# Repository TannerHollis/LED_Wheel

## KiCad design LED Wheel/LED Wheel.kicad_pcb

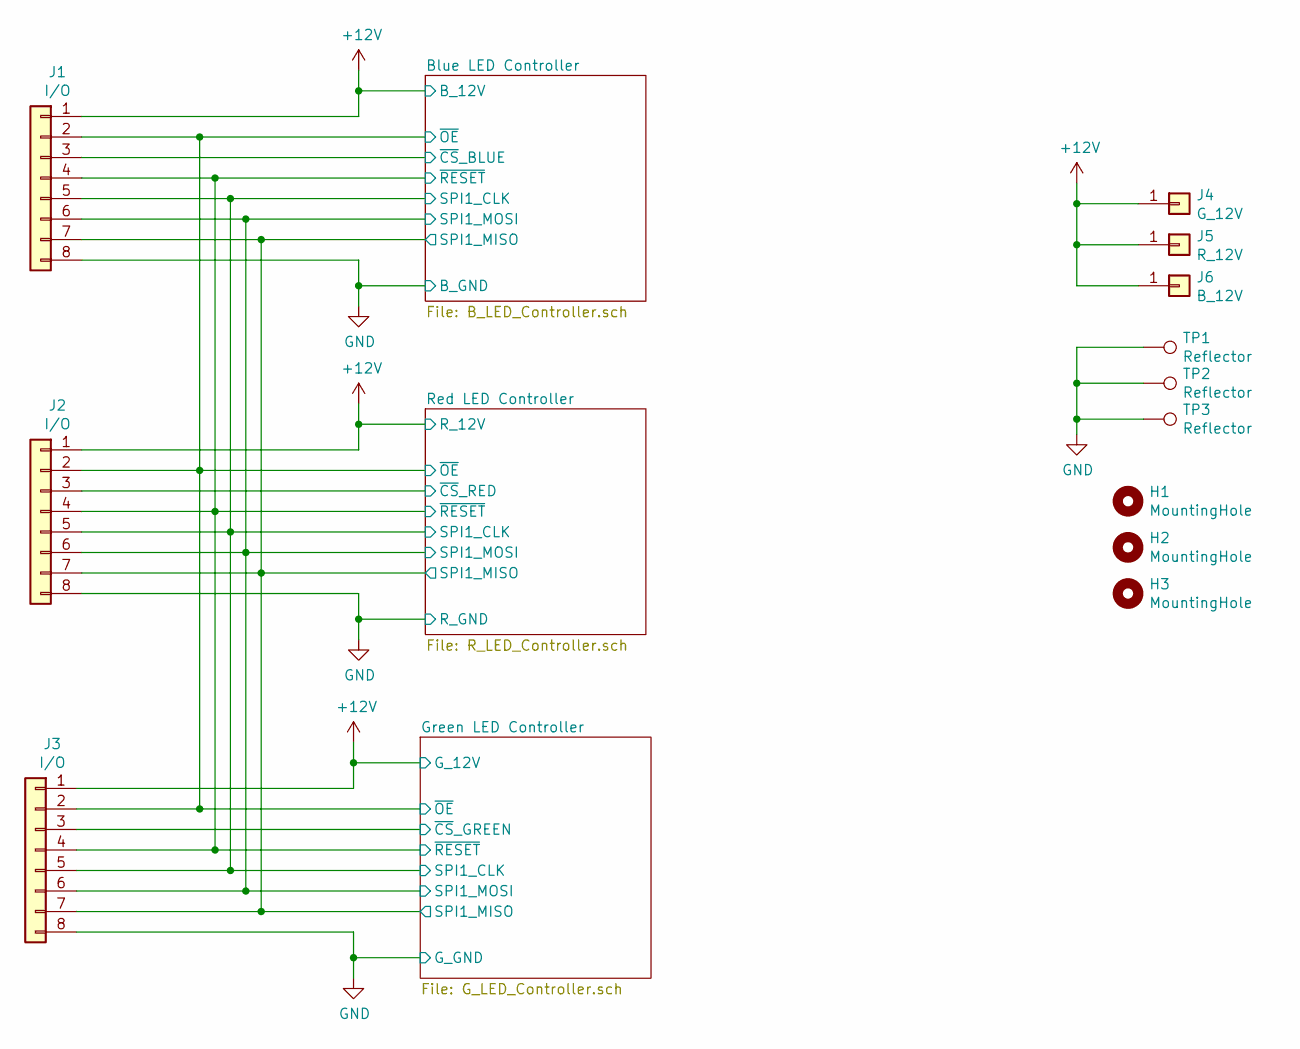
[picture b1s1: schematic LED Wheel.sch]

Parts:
H1, H2, H3: MountingHole; MountingHole_2.2mm_M2
J1, J2, J3: I/O; PinHeader_1x08_P1.27mm_Vertical
J4: G_12V; PinHeader_1x01_P2.54mm_Vertical
J5: R_12V; PinHeader_1x01_P2.54mm_Vertical
J6: B_12V; PinHeader_1x01_P2.54mm_Vertical
TP1, TP2, TP3: Reflector; Reflector 2x4mm

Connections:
+12V: J1.1, J2.1, J3.1, J4.1, J5.1, J6.1; also elsewhere on the board
/Blue LED Controller/SPI1_CLK: J1.5, J2.5, J3.5; also elsewhere on the board
/Blue LED Controller/~CS~_BLUE: J1.3; also elsewhere on the board
/Blue LED Controller/~OE~: J1.2, J2.2, J3.2; also elsewhere on the board
/Blue LED Controller/~RESET~: J1.4, J2.4, J3.4; also elsewhere on the board
/Green LED Controller/~CS~_GREEN: J3.3; also elsewhere on the board
/Red LED Controller/~CS~_RED: J2.3; also elsewhere on the board
EP: J1.8, J2.8, J3.8, TP1.1, TP2.1, TP3.1; also elsewhere on the board

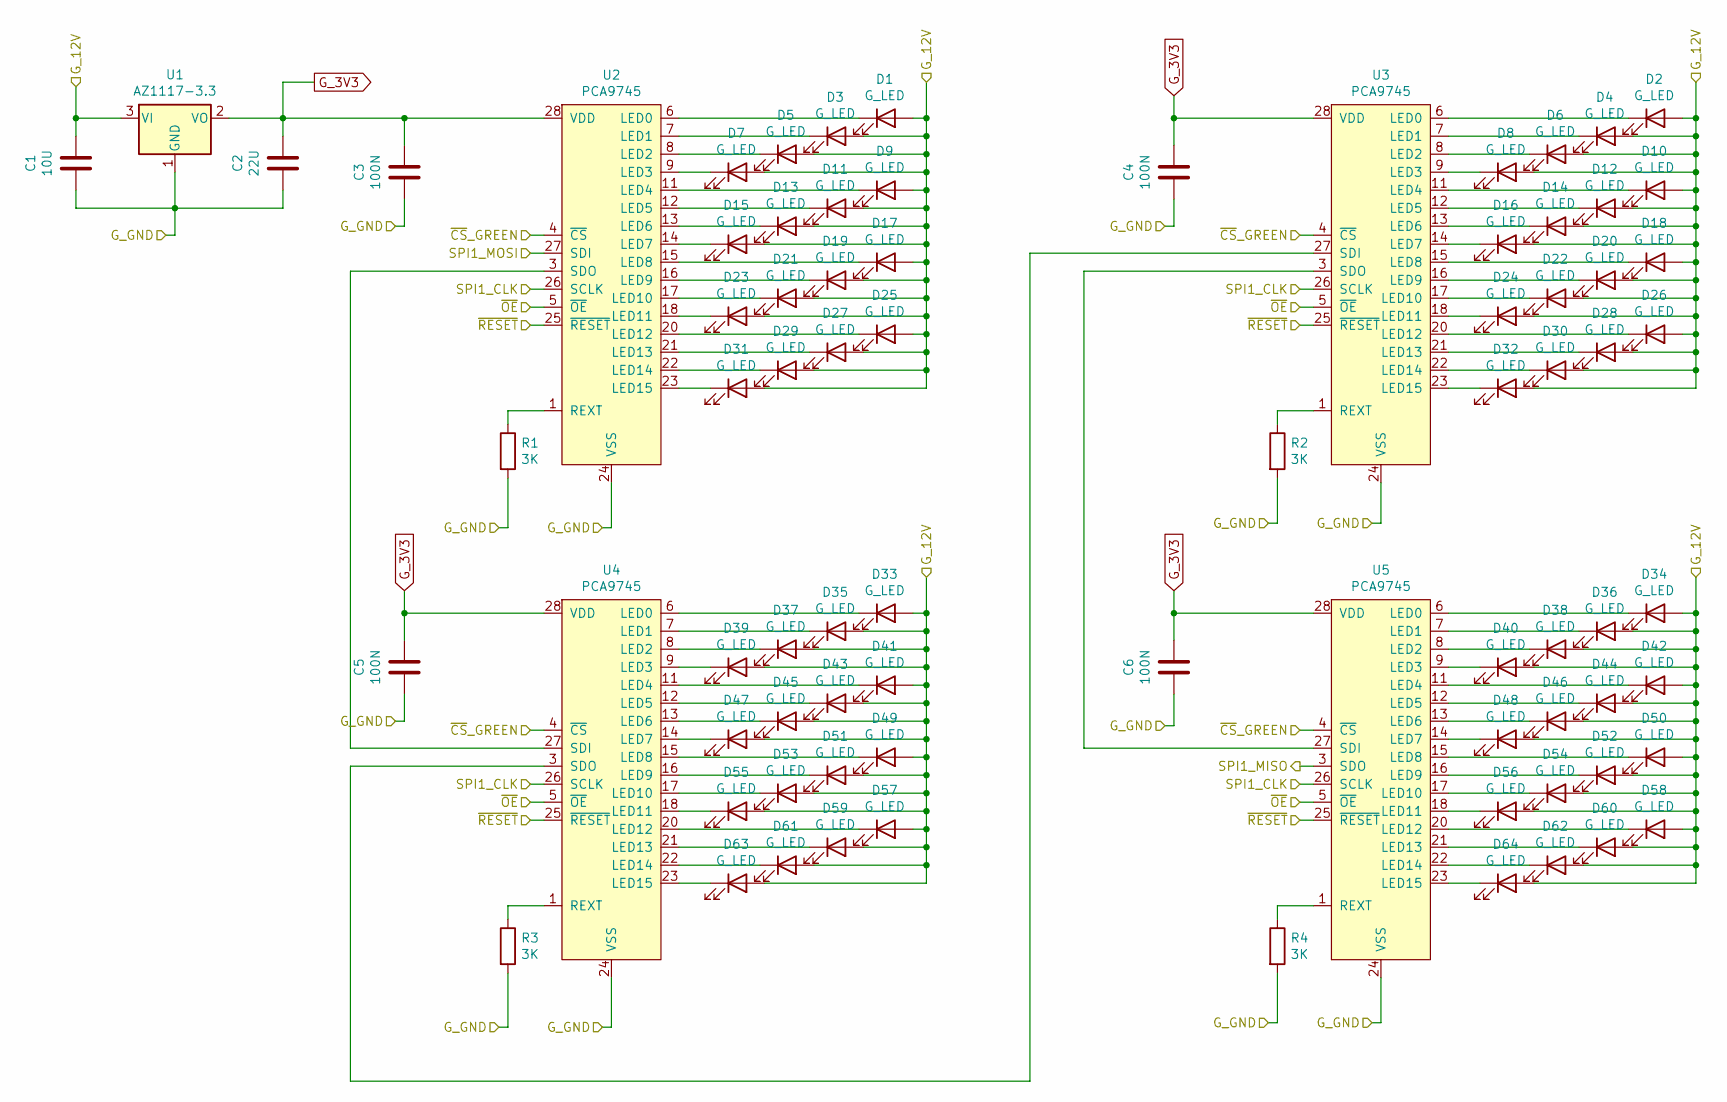
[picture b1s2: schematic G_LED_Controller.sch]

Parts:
C1: 10U; C_0603_1608Metric_Pad1.08x0.95mm_HandSolder
C2: 22U; C_0603_1608Metric_Pad1.08x0.95mm_HandSolder
C3, C4, C5, C6: 100N; C_0603_1608Metric_Pad1.08x0.95mm_HandSolder
D1, D2, D3, D4, D5, D6, D7, D8, D9, D10, D11, D12, D13, D14, D15, D16, D17, D18, D19, D20, D21, D22, D23, D24, D25, D26, D27, D28, D29, D30, D31, D32, D33, D34, D35, D36, D37, D38, D39, D40, D41, D42, D43, D44, D45, D46, D47, D48, D49, D50, D51, D52, D53, D54, D55, D56, D57, D58, D59, D60, D61, D62, D63, D64: G_LED; LED_0805_2012Metric_Pad1.15x1.40mm_HandSolder
R1, R2, R3, R4: 3K; R_1206_3216Metric_Pad1.30x1.75mm_HandSolder
U1: AZ1117-3.3; SOT-89-3_Handsoldering
U2, U3, U4, U5: PCA9745; HTSSOP-28-1EP_4.4x9.7mm_P0.65mm_EP2.85x5.4mm

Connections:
+12V: C1.1, D1.2 (A), D2.2 (A), D3.2 (A), D4.2 (A), D5.2 (A), D6.2 (A), D7.2 (A), D8.2 (A), D9.2 (A), D10.2 (A), D11.2 (A), D12.2 (A), D13.2 (A), D14.2 (A), D15.2 (A), D16.2 (A), D17.2 (A), D18.2 (A), D19.2 (A), D20.2 (A), D21.2 (A), D22.2 (A), D23.2 (A), D24.2 (A), D25.2 (A), D26.2 (A), D27.2 (A), D28.2 (A), D29.2 (A), D30.2 (A), D31.2 (A), D32.2 (A), D33.2 (A), D34.2 (A), D35.2 (A), D36.2 (A), D37.2 (A), D38.2 (A), D39.2 (A), D40.2 (A), D41.2 (A), D42.2 (A), D43.2 (A), D44.2 (A), D45.2 (A), D46.2 (A), D47.2 (A), D48.2 (A), D49.2 (A), D50.2 (A), D51.2 (A), D52.2 (A), D53.2 (A), D54.2 (A), D55.2 (A), D56.2 (A), D57.2 (A), D58.2 (A), D59.2 (A), D60.2 (A), D61.2 (A), D62.2 (A), D63.2 (A), D64.2 (A), U1.3 (VI); also elsewhere on the board
/Blue LED Controller/SPI1_CLK: U2.26 (SCLK), U3.26 (SCLK), U4.26 (SCLK), U5.26 (SCLK); also elsewhere on the board
/Blue LED Controller/~OE~: U2.5 (~OE~), U3.5 (~OE~), U4.5 (~OE~), U5.5 (~OE~); also elsewhere on the board
/Blue LED Controller/~RESET~: U2.25 (~RESET~), U3.25 (~RESET~), U4.25 (~RESET~), U5.25 (~RESET~); also elsewhere on the board
/Green LED Controller/~CS~_GREEN: U2.4 (~CS~), U3.4 (~CS~), U4.4 (~CS~), U5.4 (~CS~); also elsewhere on the board
EP: C1.2, C2.2, C3.2, C4.2, C5.2, C6.2, R1.2, R2.2, R3.2, R4.2, U1.1 (GND), U2.2 (VSS), U2.10 (VSS), U2.19 (VSS), U2.24 (VSS), U2.29 (EP), U3.2 (VSS), U3.10 (VSS), U3.19 (VSS), U3.24 (VSS), U3.29 (EP), U4.2 (VSS), U4.10 (VSS), U4.19 (VSS), U4.24 (VSS), U4.29 (EP), U5.2 (VSS), U5.10 (VSS), U5.19 (VSS), U5.24 (VSS), U5.29 (EP); also elsewhere on the board
G_3V3: C2.1, C3.1, C4.1, C5.1, C6.1, U1.2 (VO), U2.28 (VDD), U3.28 (VDD), U4.28 (VDD), U5.28 (VDD)
unnamed: D1.1 (K), U2.6 (LED0)
unnamed: D2.1 (K), U3.6 (LED0)
unnamed: D3.1 (K), U2.7 (LED1)
unnamed: D4.1 (K), U3.7 (LED1)
unnamed: D5.1 (K), U2.8 (LED2)
unnamed: D6.1 (K), U3.8 (LED2)
unnamed: D7.1 (K), U2.9 (LED3)
unnamed: D8.1 (K), U3.9 (LED3)
unnamed: D9.1 (K), U2.11 (LED4)
unnamed: D10.1 (K), U3.11 (LED4)
unnamed: D11.1 (K), U2.12 (LED5)
unnamed: D12.1 (K), U3.12 (LED5)
unnamed: D13.1 (K), U2.13 (LED6)
unnamed: D14.1 (K), U3.13 (LED6)
unnamed: D15.1 (K), U2.14 (LED7)
unnamed: D16.1 (K), U3.14 (LED7)
unnamed: D17.1 (K), U2.15 (LED8)
unnamed: D18.1 (K), U3.15 (LED8)
unnamed: D19.1 (K), U2.16 (LED9)
unnamed: D20.1 (K), U3.16 (LED9)
unnamed: D21.1 (K), U2.17 (LED10)
unnamed: D22.1 (K), U3.17 (LED10)
unnamed: D23.1 (K), U2.18 (LED11)
unnamed: D24.1 (K), U3.18 (LED11)
unnamed: D25.1 (K), U2.20 (LED12)
unnamed: D26.1 (K), U3.20 (LED12)
unnamed: D27.1 (K), U2.21 (LED13)
unnamed: D28.1 (K), U3.21 (LED13)
unnamed: D29.1 (K), U2.22 (LED14)
unnamed: D30.1 (K), U3.22 (LED14)
unnamed: D31.1 (K), U2.23 (LED15)
unnamed: D32.1 (K), U3.23 (LED15)
unnamed: D33.1 (K), U4.6 (LED0)
unnamed: D34.1 (K), U5.6 (LED0)
unnamed: D35.1 (K), U4.7 (LED1)
unnamed: D36.1 (K), U5.7 (LED1)
unnamed: D37.1 (K), U4.8 (LED2)
unnamed: D38.1 (K), U5.8 (LED2)
unnamed: D39.1 (K), U4.9 (LED3)
unnamed: D40.1 (K), U5.9 (LED3)
unnamed: D41.1 (K), U4.11 (LED4)
unnamed: D42.1 (K), U5.11 (LED4)
unnamed: D43.1 (K), U4.12 (LED5)
unnamed: D44.1 (K), U5.12 (LED5)
unnamed: D45.1 (K), U4.13 (LED6)
unnamed: D46.1 (K), U5.13 (LED6)
unnamed: D47.1 (K), U4.14 (LED7)
unnamed: D48.1 (K), U5.14 (LED7)
unnamed: D49.1 (K), U4.15 (LED8)
unnamed: D50.1 (K), U5.15 (LED8)
unnamed: D51.1 (K), U4.16 (LED9)
unnamed: D52.1 (K), U5.16 (LED9)
unnamed: D53.1 (K), U4.17 (LED10)
unnamed: D54.1 (K), U5.17 (LED10)
unnamed: D55.1 (K), U4.18 (LED11)
unnamed: D56.1 (K), U5.18 (LED11)
unnamed: D57.1 (K), U4.20 (LED12)
unnamed: D58.1 (K), U5.20 (LED12)
unnamed: D59.1 (K), U4.21 (LED13)
unnamed: D60.1 (K), U5.21 (LED13)
unnamed: D61.1 (K), U4.22 (LED14)
unnamed: D62.1 (K), U5.22 (LED14)
unnamed: D63.1 (K), U4.23 (LED15)
unnamed: D64.1 (K), U5.23 (LED15)
unnamed: R1.1, U2.1 (REXT)
unnamed: R2.1, U3.1 (REXT)
unnamed: R3.1, U4.1 (REXT)
unnamed: R4.1, U5.1 (REXT)

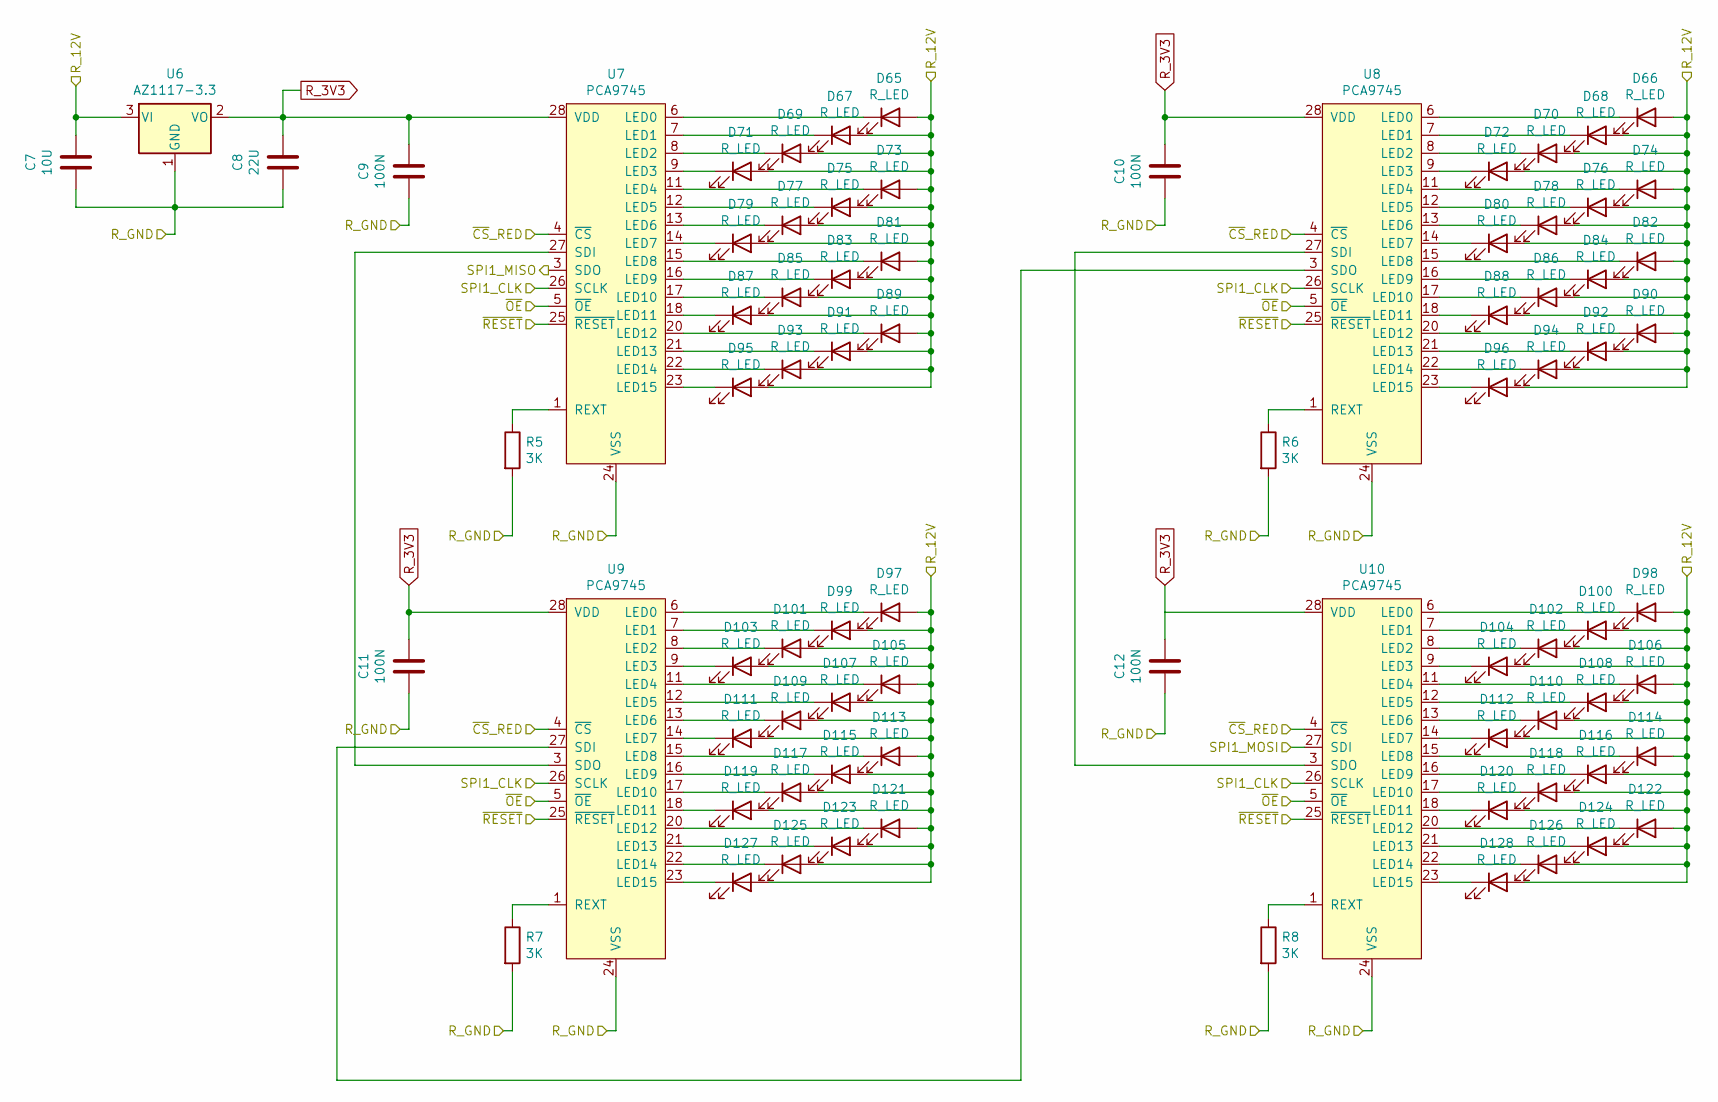
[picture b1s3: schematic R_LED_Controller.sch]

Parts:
C7: 10U; C_0603_1608Metric_Pad1.08x0.95mm_HandSolder
C8: 22U; C_0603_1608Metric_Pad1.08x0.95mm_HandSolder
C9, C10, C11, C12: 100N; C_0603_1608Metric_Pad1.08x0.95mm_HandSolder
D65, D66, D67, D68, D69, D70, D71, D72, D73, D74, D75, D76, D77, D78, D79, D80, D81, D82, D83, D84, D85, D86, D87, D88, D89, D90, D91, D92, D93, D94, D95, D96, D97, D98, D99, D100, D101, D102, D103, D104, D105, D106, D107, D108, D109, D110, D111, D112, D113, D114, D115, D116, D117, D118, D119, D120, D121, D122, D123, D124, D125, D126, D127, D128: R_LED; LED_0805_2012Metric_Pad1.15x1.40mm_HandSolder
R5, R6, R7, R8: 3K; R_1206_3216Metric_Pad1.30x1.75mm_HandSolder
U6: AZ1117-3.3; SOT-89-3_Handsoldering
U7, U8, U9, U10: PCA9745; HTSSOP-28-1EP_4.4x9.7mm_P0.65mm_EP2.85x5.4mm

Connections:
+12V: C7.1, D65.2 (A), D66.2 (A), D67.2 (A), D68.2 (A), D69.2 (A), D70.2 (A), D71.2 (A), D72.2 (A), D73.2 (A), D74.2 (A), D75.2 (A), D76.2 (A), D77.2 (A), D78.2 (A), D79.2 (A), D80.2 (A), D81.2 (A), D82.2 (A), D83.2 (A), D84.2 (A), D85.2 (A), D86.2 (A), D87.2 (A), D88.2 (A), D89.2 (A), D90.2 (A), D91.2 (A), D92.2 (A), D93.2 (A), D94.2 (A), D95.2 (A), D96.2 (A), D97.2 (A), D98.2 (A), D99.2 (A), D100.2 (A), D101.2 (A), D102.2 (A), D103.2 (A), D104.2 (A), D105.2 (A), D106.2 (A), D107.2 (A), D108.2 (A), D109.2 (A), D110.2 (A), D111.2 (A), D112.2 (A), D113.2 (A), D114.2 (A), D115.2 (A), D116.2 (A), D117.2 (A), D118.2 (A), D119.2 (A), D120.2 (A), D121.2 (A), D122.2 (A), D123.2 (A), D124.2 (A), D125.2 (A), D126.2 (A), D127.2 (A), D128.2 (A), U6.3 (VI); also elsewhere on the board
/Blue LED Controller/SPI1_CLK: U7.26 (SCLK), U8.26 (SCLK), U9.26 (SCLK), U10.26 (SCLK); also elsewhere on the board
/Blue LED Controller/~OE~: U7.5 (~OE~), U8.5 (~OE~), U9.5 (~OE~), U10.5 (~OE~); also elsewhere on the board
/Blue LED Controller/~RESET~: U7.25 (~RESET~), U8.25 (~RESET~), U9.25 (~RESET~), U10.25 (~RESET~); also elsewhere on the board
/Red LED Controller/~CS~_RED: U7.4 (~CS~), U8.4 (~CS~), U9.4 (~CS~), U10.4 (~CS~); also elsewhere on the board
EP: C7.2, C8.2, C9.2, C10.2, C11.2, C12.2, R5.2, R6.2, R7.2, R8.2, U6.1 (GND), U7.2 (VSS), U7.10 (VSS), U7.19 (VSS), U7.24 (VSS), U7.29 (EP), U8.2 (VSS), U8.10 (VSS), U8.19 (VSS), U8.24 (VSS), U8.29 (EP), U9.2 (VSS), U9.10 (VSS), U9.19 (VSS), U9.24 (VSS), U9.29 (EP), U10.2 (VSS), U10.10 (VSS), U10.19 (VSS), U10.24 (VSS), U10.29 (EP); also elsewhere on the board
unnamed: D65.1 (K), U7.6 (LED0)
unnamed: D66.1 (K), U8.6 (LED0)
unnamed: D67.1 (K), U7.7 (LED1)
unnamed: D68.1 (K), U8.7 (LED1)
unnamed: D69.1 (K), U7.8 (LED2)
unnamed: D70.1 (K), U8.8 (LED2)
unnamed: D71.1 (K), U7.9 (LED3)
unnamed: D72.1 (K), U8.9 (LED3)
unnamed: D73.1 (K), U7.11 (LED4)
unnamed: D74.1 (K), U8.11 (LED4)
unnamed: D75.1 (K), U7.12 (LED5)
unnamed: D76.1 (K), U8.12 (LED5)
unnamed: D77.1 (K), U7.13 (LED6)
unnamed: D78.1 (K), U8.13 (LED6)
unnamed: D79.1 (K), U7.14 (LED7)
unnamed: D80.1 (K), U8.14 (LED7)
unnamed: D81.1 (K), U7.15 (LED8)
unnamed: D82.1 (K), U8.15 (LED8)
unnamed: D83.1 (K), U7.16 (LED9)
unnamed: D84.1 (K), U8.16 (LED9)
unnamed: D85.1 (K), U7.17 (LED10)
unnamed: D86.1 (K), U8.17 (LED10)
unnamed: D87.1 (K), U7.18 (LED11)
unnamed: D88.1 (K), U8.18 (LED11)
unnamed: D89.1 (K), U7.20 (LED12)
unnamed: D90.1 (K), U8.20 (LED12)
unnamed: D91.1 (K), U7.21 (LED13)
unnamed: D92.1 (K), U8.21 (LED13)
unnamed: D93.1 (K), U7.22 (LED14)
unnamed: D94.1 (K), U8.22 (LED14)
unnamed: D95.1 (K), U7.23 (LED15)
unnamed: D96.1 (K), U8.23 (LED15)
unnamed: D97.1 (K), U9.6 (LED0)
unnamed: D98.1 (K), U10.6 (LED0)
unnamed: D99.1 (K), U9.7 (LED1)
unnamed: D100.1 (K), U10.7 (LED1)
unnamed: D101.1 (K), U9.8 (LED2)
unnamed: D102.1 (K), U10.8 (LED2)
unnamed: D103.1 (K), U9.9 (LED3)
unnamed: D104.1 (K), U10.9 (LED3)
unnamed: D105.1 (K), U9.11 (LED4)
unnamed: D106.1 (K), U10.11 (LED4)
unnamed: D107.1 (K), U9.12 (LED5)
unnamed: D108.1 (K), U10.12 (LED5)
unnamed: D109.1 (K), U9.13 (LED6)
unnamed: D110.1 (K), U10.13 (LED6)
unnamed: D111.1 (K), U9.14 (LED7)
unnamed: D112.1 (K), U10.14 (LED7)
unnamed: D113.1 (K), U9.15 (LED8)
unnamed: D114.1 (K), U10.15 (LED8)
unnamed: D115.1 (K), U9.16 (LED9)
unnamed: D116.1 (K), U10.16 (LED9)
unnamed: D117.1 (K), U9.17 (LED10)
unnamed: D118.1 (K), U10.17 (LED10)
unnamed: D119.1 (K), U9.18 (LED11)
unnamed: D120.1 (K), U10.18 (LED11)
unnamed: D121.1 (K), U9.20 (LED12)
unnamed: D122.1 (K), U10.20 (LED12)
unnamed: D123.1 (K), U9.21 (LED13)
unnamed: D124.1 (K), U10.21 (LED13)
unnamed: D125.1 (K), U9.22 (LED14)
unnamed: D126.1 (K), U10.22 (LED14)
unnamed: D127.1 (K), U9.23 (LED15)
unnamed: D128.1 (K), U10.23 (LED15)
unnamed: R5.1, U7.1 (REXT)
unnamed: R6.1, U8.1 (REXT)
unnamed: R7.1, U9.1 (REXT)
unnamed: R8.1, U10.1 (REXT)
unnamed: U7.27 (SDI), U9.3 (SDO)
unnamed: U8.3 (SDO), U9.27 (SDI)
unnamed: U8.27 (SDI), U10.3 (SDO)
R_3V3: C8.1, C9.1, C10.1, C11.1, C12.1, U6.2 (VO), U7.28 (VDD), U8.28 (VDD), U9.28 (VDD), U10.28 (VDD)

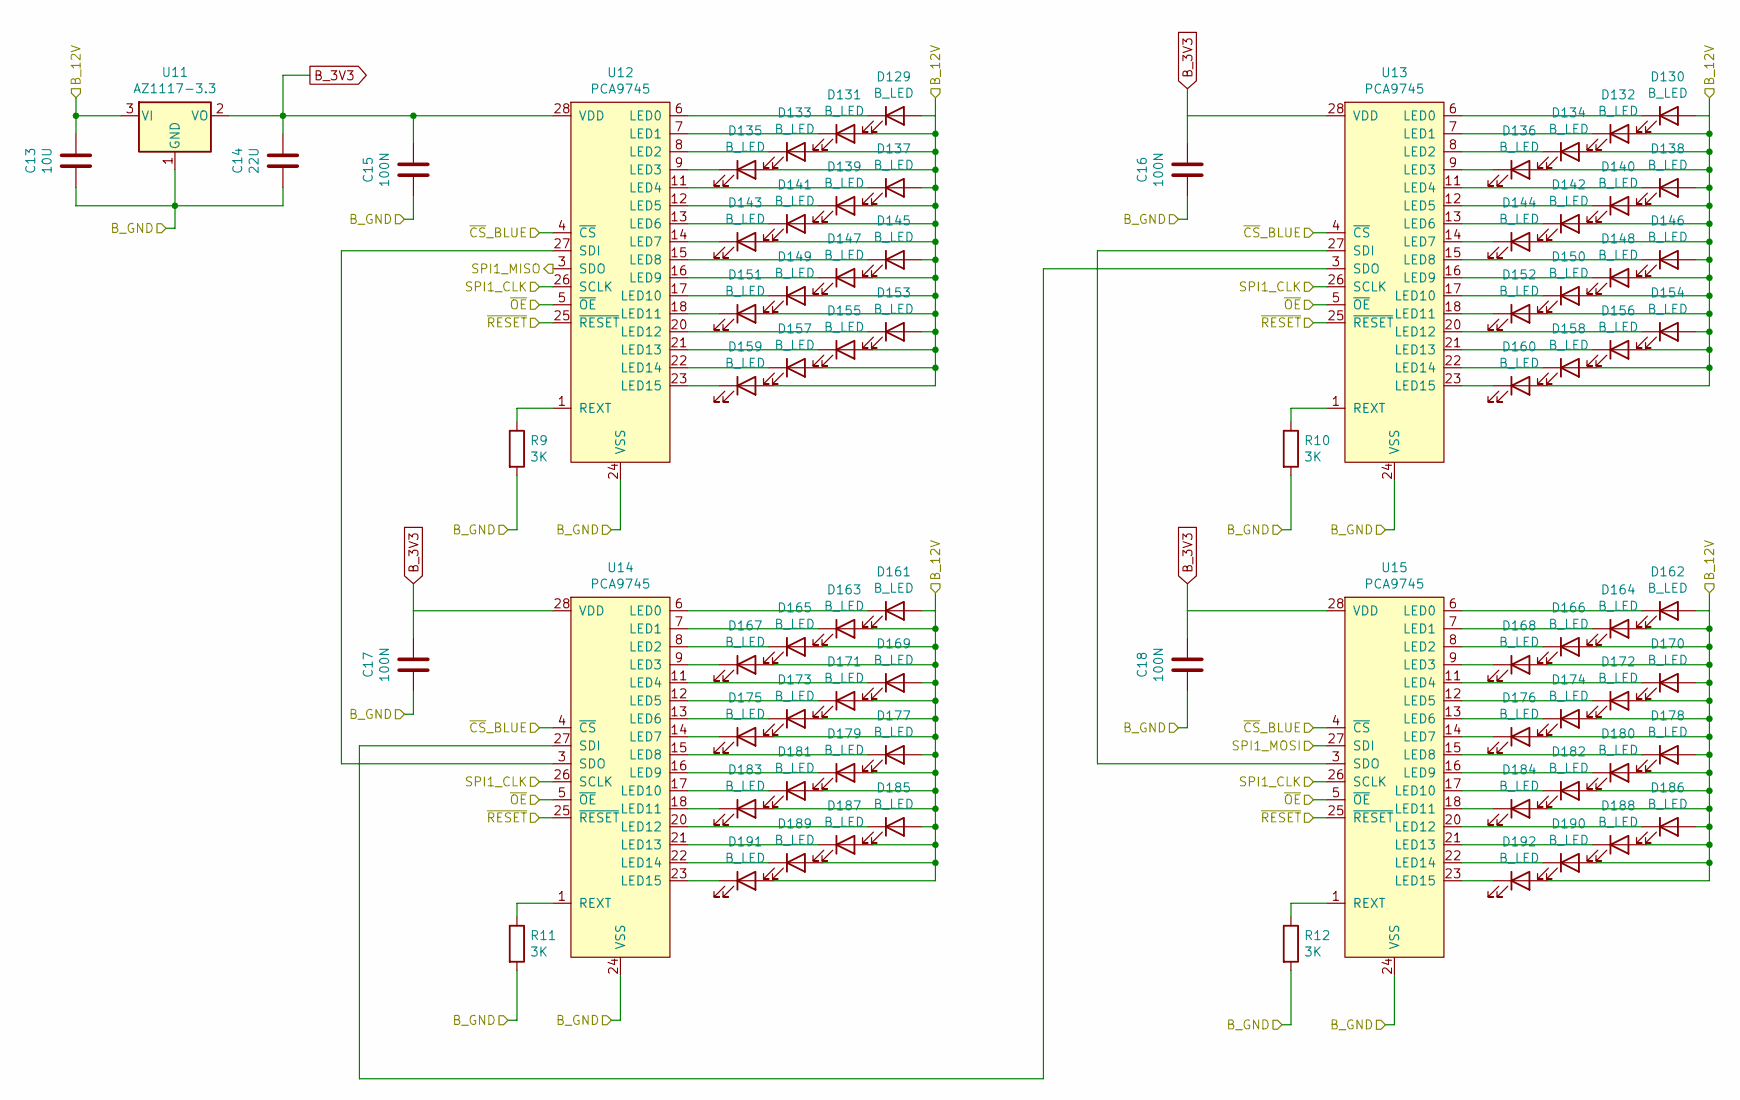
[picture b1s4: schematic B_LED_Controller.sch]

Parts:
C13: 10U; C_0603_1608Metric_Pad1.08x0.95mm_HandSolder
C14: 22U; C_0603_1608Metric_Pad1.08x0.95mm_HandSolder
C15, C16, C17, C18: 100N; C_0603_1608Metric_Pad1.08x0.95mm_HandSolder
D129, D130, D131, D132, D133, D134, D135, D136, D137, D138, D139, D140, D141, D142, D143, D144, D145, D146, D147, D148, D149, D150, D151, D152, D153, D154, D155, D156, D157, D158, D159, D160, D161, D162, D163, D164, D165, D166, D167, D168, D169, D170, D171, D172, D173, D174, D175, D176, D177, D178, D179, D180, D181, D182, D183, D184, D185, D186, D187, D188, D189, D190, D191, D192: B_LED; LED_0805_2012Metric_Pad1.15x1.40mm_HandSolder
R9, R10, R11, R12: 3K; R_1206_3216Metric_Pad1.30x1.75mm_HandSolder
U11: AZ1117-3.3; SOT-89-3_Handsoldering
U12, U13, U14, U15: PCA9745; HTSSOP-28-1EP_4.4x9.7mm_P0.65mm_EP2.85x5.4mm

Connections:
+12V: C13.1, D129.2 (A), D130.2 (A), D131.2 (A), D132.2 (A), D133.2 (A), D134.2 (A), D135.2 (A), D136.2 (A), D137.2 (A), D138.2 (A), D139.2 (A), D140.2 (A), D141.2 (A), D142.2 (A), D143.2 (A), D144.2 (A), D145.2 (A), D146.2 (A), D147.2 (A), D148.2 (A), D149.2 (A), D150.2 (A), D151.2 (A), D152.2 (A), D153.2 (A), D154.2 (A), D155.2 (A), D156.2 (A), D157.2 (A), D158.2 (A), D159.2 (A), D160.2 (A), D161.2 (A), D162.2 (A), D163.2 (A), D164.2 (A), D165.2 (A), D166.2 (A), D167.2 (A), D168.2 (A), D169.2 (A), D170.2 (A), D171.2 (A), D172.2 (A), D173.2 (A), D174.2 (A), D175.2 (A), D176.2 (A), D177.2 (A), D178.2 (A), D179.2 (A), D180.2 (A), D181.2 (A), D182.2 (A), D183.2 (A), D184.2 (A), D185.2 (A), D186.2 (A), D187.2 (A), D188.2 (A), D189.2 (A), D190.2 (A), D191.2 (A), D192.2 (A), U11.3 (VI); also elsewhere on the board
/Blue LED Controller/SPI1_CLK: U12.26 (SCLK), U13.26 (SCLK), U14.26 (SCLK), U15.26 (SCLK); also elsewhere on the board
/Blue LED Controller/~CS~_BLUE: U12.4 (~CS~), U13.4 (~CS~), U14.4 (~CS~), U15.4 (~CS~); also elsewhere on the board
/Blue LED Controller/~OE~: U12.5 (~OE~), U13.5 (~OE~), U14.5 (~OE~), U15.5 (~OE~); also elsewhere on the board
/Blue LED Controller/~RESET~: U12.25 (~RESET~), U13.25 (~RESET~), U14.25 (~RESET~), U15.25 (~RESET~); also elsewhere on the board
B_3V3: C14.1, C15.1, C16.1, C17.1, C18.1, U11.2 (VO), U12.28 (VDD), U13.28 (VDD), U14.28 (VDD), U15.28 (VDD)
EP: C13.2, C14.2, C15.2, C16.2, C17.2, C18.2, R9.2, R10.2, R11.2, R12.2, U11.1 (GND), U12.2 (VSS), U12.10 (VSS), U12.19 (VSS), U12.24 (VSS), U12.29 (EP), U13.2 (VSS), U13.10 (VSS), U13.19 (VSS), U13.24 (VSS), U13.29 (EP), U14.2 (VSS), U14.10 (VSS), U14.19 (VSS), U14.24 (VSS), U14.29 (EP), U15.2 (VSS), U15.10 (VSS), U15.19 (VSS), U15.24 (VSS), U15.29 (EP); also elsewhere on the board
unnamed: D129.1 (K), U12.6 (LED0)
unnamed: D130.1 (K), U13.6 (LED0)
unnamed: D131.1 (K), U12.7 (LED1)
unnamed: D132.1 (K), U13.7 (LED1)
unnamed: D133.1 (K), U12.8 (LED2)
unnamed: D134.1 (K), U13.8 (LED2)
unnamed: D135.1 (K), U12.9 (LED3)
unnamed: D136.1 (K), U13.9 (LED3)
unnamed: D137.1 (K), U12.11 (LED4)
unnamed: D138.1 (K), U13.11 (LED4)
unnamed: D139.1 (K), U12.12 (LED5)
unnamed: D140.1 (K), U13.12 (LED5)
unnamed: D141.1 (K), U12.13 (LED6)
unnamed: D142.1 (K), U13.13 (LED6)
unnamed: D143.1 (K), U12.14 (LED7)
unnamed: D144.1 (K), U13.14 (LED7)
unnamed: D145.1 (K), U12.15 (LED8)
unnamed: D146.1 (K), U13.15 (LED8)
unnamed: D147.1 (K), U12.16 (LED9)
unnamed: D148.1 (K), U13.16 (LED9)
unnamed: D149.1 (K), U12.17 (LED10)
unnamed: D150.1 (K), U13.17 (LED10)
unnamed: D151.1 (K), U12.18 (LED11)
unnamed: D152.1 (K), U13.18 (LED11)
unnamed: D153.1 (K), U12.20 (LED12)
unnamed: D154.1 (K), U13.20 (LED12)
unnamed: D155.1 (K), U12.21 (LED13)
unnamed: D156.1 (K), U13.21 (LED13)
unnamed: D157.1 (K), U12.22 (LED14)
unnamed: D158.1 (K), U13.22 (LED14)
unnamed: D159.1 (K), U12.23 (LED15)
unnamed: D160.1 (K), U13.23 (LED15)
unnamed: D161.1 (K), U14.6 (LED0)
unnamed: D162.1 (K), U15.6 (LED0)
unnamed: D163.1 (K), U14.7 (LED1)
unnamed: D164.1 (K), U15.7 (LED1)
unnamed: D165.1 (K), U14.8 (LED2)
unnamed: D166.1 (K), U15.8 (LED2)
unnamed: D167.1 (K), U14.9 (LED3)
unnamed: D168.1 (K), U15.9 (LED3)
unnamed: D169.1 (K), U14.11 (LED4)
unnamed: D170.1 (K), U15.11 (LED4)
unnamed: D171.1 (K), U14.12 (LED5)
unnamed: D172.1 (K), U15.12 (LED5)
unnamed: D173.1 (K), U14.13 (LED6)
unnamed: D174.1 (K), U15.13 (LED6)
unnamed: D175.1 (K), U14.14 (LED7)
unnamed: D176.1 (K), U15.14 (LED7)
unnamed: D177.1 (K), U14.15 (LED8)
unnamed: D178.1 (K), U15.15 (LED8)
unnamed: D179.1 (K), U14.16 (LED9)
unnamed: D180.1 (K), U15.16 (LED9)
unnamed: D181.1 (K), U14.17 (LED10)
unnamed: D182.1 (K), U15.17 (LED10)
unnamed: D183.1 (K), U14.18 (LED11)
unnamed: D184.1 (K), U15.18 (LED11)
unnamed: D185.1 (K), U14.20 (LED12)
unnamed: D186.1 (K), U15.20 (LED12)
unnamed: D187.1 (K), U14.21 (LED13)
unnamed: D188.1 (K), U15.21 (LED13)
unnamed: D189.1 (K), U14.22 (LED14)
unnamed: D190.1 (K), U15.22 (LED14)
unnamed: D191.1 (K), U14.23 (LED15)
unnamed: D192.1 (K), U15.23 (LED15)
unnamed: R9.1, U12.1 (REXT)
unnamed: R10.1, U13.1 (REXT)
unnamed: R11.1, U14.1 (REXT)
unnamed: R12.1, U15.1 (REXT)
unnamed: U12.27 (SDI), U14.3 (SDO)
unnamed: U13.3 (SDO), U14.27 (SDI)
unnamed: U13.27 (SDI), U15.3 (SDO)

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
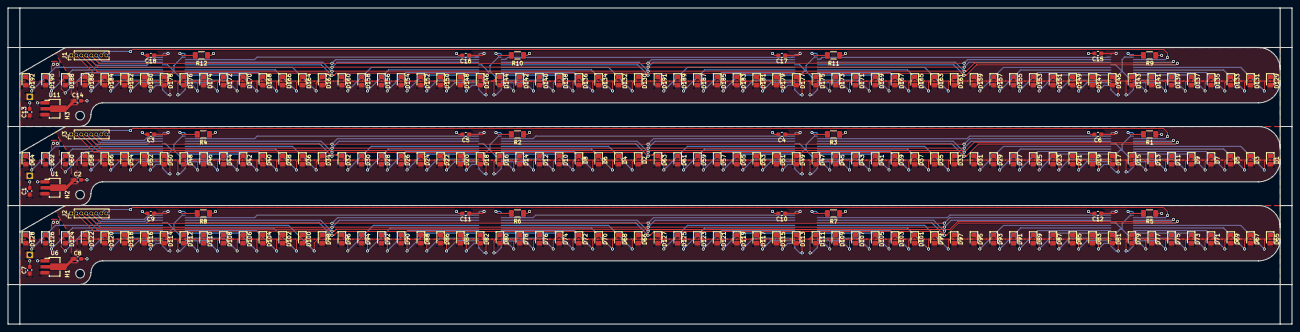
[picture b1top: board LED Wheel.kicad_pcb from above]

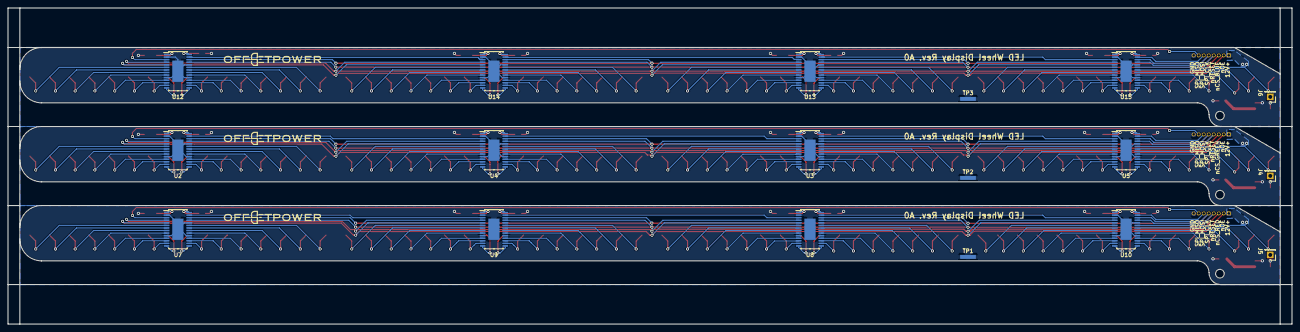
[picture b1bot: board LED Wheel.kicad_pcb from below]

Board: 2 copper layers, 325.0 x 80.0 mm, 249 parts (15 on the bottom side), 226 nets.

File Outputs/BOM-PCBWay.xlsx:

|  |  | xxxx xxxx xxxxx xxPCS BOM
Item # | *Designator | *Qty | Manufacturer | *Mfg Part # | Description / Value | *Package/Footprint | Type | Your Instructions / Notes
1 | C1, C7, C13 | 3 |  |  | 10U | SMD: 0603 | SMD | Generic 0603 10U 25V
2 | C2, C8, C14 | 3 |  |  | 22U | SMD: 0603 | SMD | Generic 0603 22U 6.3V
3 | C3, C4, C5, C6, C9, C10, C11, C12, C15, C16, C17, C18 | 12 |  |  | 100N | SMD: 0603 | SMD | Generic 0603 100N 6.3V
4 | D1, D2, D3, D4, D5, D6, D7, D8, D9, D10, D11, D12, D13, D14, D15, D16, D17, D18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 | 64 |  |  | G_LED | SMD: 0805 | SMD | Generic 0805 Green LED Diffused
5 | D65, D66, D67, D68, D69, D70, D71, D72, D73, D74, D75, D76, D77, D78, D79, D80,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 | 64 |  |  | R_LED | SMD: 0805 | SMD | Generic 0805 Red LED Diffused
6 | D129, D130, D131, D132, D133, D134, D135, D136, D137, D138, D139, D140, D141, D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 | 64 |  |  | B_LED | SMD: 0805 | SMD | Generic 0805 Blue LED Diffused
7 | H1, H2, H3 | 3 |  |  | MountingHole | Mechanical:MountingHole | THT | DNP
8 | J1, J2, J3 | 3 |  |  | I/O | Connector_Generic:Conn_01x08 | THT | DNP
9 | R1, R2, R3, R4, R5, R6, R7, R8, R9, R10, R11, R12 | 12 |  |  | 3K | SMD: 1206 | SMD | Generic 1206 3K 1%
10 | U1, U6, U11 | 3 | Diodes Incorporated | AZ1117CR-3.3TRG1 | AZ1117-3.3 | SMD: SOT-89-3 | SMD
11 | U2, U3, U4, U5, U7, U8, U9, U10, U12, U13, U14, U15 | 12 | NXP Semiconductors | PCA9745BTWJ | PCA9745 | SMD: HTSSOP-28-1EP 4.4x9.7mm | SMD | DNP
Need a quick and accurante quote? Need an efficient production? Please read SMT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
Click for Instructions on How to Create a BOM

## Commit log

2021-09-08 Init Commit
    Initial Commit with the Near-Finished Board Layout
2021-09-09 Rev A0 Commit
    Files all sent to PCB manufacturer & BOM
2021-09-15 Updated LED Wheel for PCBWay
    Added Light reflector for speed sensor, updated board layout for VCut
